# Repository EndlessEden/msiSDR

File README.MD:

# SDR RSP1: SIMPLIFIED 

## DESCRIPTION

(EXPECT THIS TO BE A MESS. It's direct from my research notes!)

"SDR RSP1 Simple" often referred to by "BG7YZF", is a SDRPlay RSP1/RSP1a clone with a simplified circuit. The SDR RSP1 is a redesign of the [MSI.SDR](https://github.com/11tools/msiSDR), a clone of the SDRplay RSP1A. All of these use the Msi001 and the Msi2500 (Sometimes called Msi3001 when used in this combo) chips which according to the vendor the SDR.RSP1 "Based on a simple small production made by Gao Wan"

----------------------

## HARDWARE

In a nutshell, it's a SDR receiver with 5 bandpass filtered antenna inputs and a USB Type-C interface. With no automatic antenna switching, and soldered in-line bandpass filters.

The [msi001](./Datasheets/msi001%20datasheet.pdf) microcircuit contains 5 antenna amplifiers (each for its own range), a synthesizer and quadrature mixers outputting I/Q signals, software-controlled bandpass filters and amplifiers. 

The [msi2500](./Datasheets/msi2500%20datasheet.pdf) is a variable bit (8 to 14 bit) ADC and DSP with USB interface. 

The result is:
- a range from 10 kHz to 1 GHz (with a hole at 250-400 MHz)
- a bandwidth of up to 10 MHz,
MSPS from 2 to 6 MHz (14-bit),
MSPS from 6 to 8 MHz (12-bit),
MSPS from 8 to 9 MHz (10 bits),
MSPS from 9 to 10 MHz (8 bits).
- With a SNR of 60 dB.

the "SDR RSP1" comes in two different models. ["Simple"](https://world.taobao.com/item/647736653771.htm?spm=a21wu.11804641.0.0.508e39d3yTvEJb) and ["Full"](https://www.taobao.com/list/item/645090109900.htm), their antenna circuitry, oscillators and filtering are different. The "Full" is notably better due to being simpler to operate, having a better oscillator and improved filtering. But all of these are design choices to cut costs. Outside the headaches with the Msi001's antenna switching, all other changes done to the "Full" version are entirely possible on the "Simple" version. Some of this can be done by the user if they are experienced in SMP soldering.

----------------------

## FROM THE VENDOR

[Vendor 2](https://world.taobao.com/item/647736653771.htm?spm=a21wu.11804641.0.0.508e39d3yTvEJb) "Question: What is the difference between this(SDR RSP1 Simple) and the full (SDR RSP1 full) version you sell?"
"Answer: The full version uses 0.5PPM TCXO (Oscillators), the frequency is accurate, the simple version only uses ordinary active crystal oscillators with a small offset (not affecting reception), the simple version does not have a casing, and the antenna needs to be switched manually. The simple version is only for usability. Pursue performance. The maximum frequency of the simple version can only reach 1G, you can change it to 2G by yourself(oscillator), because the simple version has a great simplification in the circuit, and it is not as good as the full version in terms of acceptance sensitivity and selectivity, but the two are the same in function Yes ..."

[Vendor 2](https://world.taobao.com/item/647736653771.htm?spm=a21wu.11804641.0.0.508e39d3yTvEJb) "Question: Did you design this yourself, or plagiarize someone else's circuit?"
"Answer: This SDR is an open source project of the foreign SDRPLAY company. The circuit has been simplified by the smith of the domestic science and technology forum. It is also open sourced. Here is the original post [www.kechuang.org/t/83757](www.kechuang.org/t/83757). Please refer to it. I just like radio. , Try to re-engrave it by yourself and add filters in the three bands of 60MHz to 1000Mhz, redesign the PCB layout, modify the interface to Type-C, no copper in the radio frequency area, and add jumper vias to facilitate later toss."

[Vendor 3](https://www.taobao.com/list/item/645090109900.htm) "This (SDR RSP1 Full) full version has the same software functions as the simple version ("SDR RSP1 Simple"), with higher sensitivity and more powerful performance."

----------------------

## ORIGIN

The "SDR RSP1 Simple" design originates from Huanghuai University(MAKER SPACE OF HUANGHUAI UNIVERSITY[香港 创 客 空 闪])(* See HHU), research done by a member known as "Smith" on their "Domestic science and technology forum" (See [Design](https://www.kechuang.org/t/83757)). The SDR RSP1's are improvements to these designs by "BG7YZF". A self-described as "a computer science and technology undergraduate student who is engaged in radio, model aircraft, drone, and photography." on their vendor page.

The "DE BG7YZF" silk screen refers to the designer, BG7YZF (a unregistered callsign from China [DXCC Entity #318]) is from QTH Xincai County, Henan Province. [VideoD1](https://www.bilibili.com/video/BV1Co4y1D7R2/) 

The Prefix 'DE' is a Morse code abbreviation amateur radio operators use meaning "from" (See [DE-W](https://en.wikipedia.org/wiki/Amateur_radio_call_signs)). 

The vendor "家晨科創" [Jiachen Technology](https://world.taobao.com/dianpu/573333074.htm?spm=a21wu.12321156.shop-area.1.4170796aFrsOco) seems to be BG7YZF as their callsign is their literal [logo](./Images/vendor/vendor.jpg). Supporting images in the product pages suggest they are the legitimate Vendors of the board(s).

All this information is further reinforced by other silk screens on the board (See images below):

"Maker Space of Huanghuai University" (Self Explanatory)

"Research, Science, Technology and prepare to serve the motherland" (HHU Quote)

and "家晨科创" [https://t.bilibili.com/550480890268977421?tab=2](https://t.bilibili.com/550480890268977421?tab=2) This last one is literally "BG7YZF".

----------------------

### KNOWN CAVEATS

 - Software: As the 'SDR RSP1 Simple' is a modified MSI.SDR RSP1 design (Itself Based on the SDRplay RSP1A), the msi001 and msi2500 chips can natively use SDRplay's proprietary api. However, other projects based on libusb(see mirisdr4) have come along to attempt to interface with the device's raw I/Q stream Using similar methods to the now famous rtlsdr project. However, since the 'RSP1 Simple' is based on the 'RSP1A', i am unaware of how well supported it would be at this moment in time. (See: https://github.com/f4exb/libmirisdr-4/issues/2) 
 
 - Tuning: the SDR RSP1 Simple requires "manual antenna switching"(This is poorly documented!), unlike its "Full" version. As expected from its poorly documented nature, Users report "RSP1 Simple"/"BG7YZF" cannot tune out of FM broadcast frequency range (See: [Ref 1](https://forums.radioreference.com/threads/12-bit-4-antenna-ports-35-delivered.430252/page-2)/[Ref 3](https://www.reddit.com/r/RTLSDR/comments/onftps/any_feedback_on_the_bg7yzf_version_of_the_msi_001/)). Although reports show otherwise (See: [Ref 4](https://www.reddit.com/r/RTLSDR/comments/qnlfwq/rsp1_chinese_clone_reviewissues/)) | As mentioned, the antennas have to be manually "Switched", The Msi001 is entirely capable of tuning frequency separated antennas, thus its design. However, switching antenna sources seems to be something that has to be done at the msi001(Tuner)'s initialisation. This is all very poorly documented and even the vendor does not  document this properly. Only vaguely mentioning it in an additional "Faq" area at the bottom of their product advert... | I will review and document what i learn when i have more time to understand the issue. I have yet to test the device at all, so i have no idea of its functionality as of yet.
 
 - USB 2.0 Type-C: USB-C interface seems to have several datalines not connected, suggesting it can only achieve USB 2.0 "High-Speed" speeds. While this should be fine (in theory), it may limit bandwidth in some circumstances. The Msi2500's USB Interface is unknown to me at the time of writing, so its suggested it follows USB 1.1/2.0 specifications. limiting many factors including the length of the cable significantly. This is due to power limitations that USB2.0 specification lays out not allowing more than 5v/0.5A(500mA), or 2.5w power draw. This limitation prevents long cable lengths due to the loss experienced at 3M, limiting it to a theoretical maximum of 5m. | Something Usb3.0+ partially overcame with power specification changes. Most importantly this allows for in-line Active USB cables instead of passive, extending length to up to 50M with limited loss. All of this is mute if in fact Msi001 is usb 2.0 only, but if it is capable of 3.0, then the wiring is a design fault for certain.
 
 - Undocumented Variants: Design has Undocumented variants (See: [R4-E](https://www.ebay.com/itm/255106602228)) as seen in The Ebay listing shared in [Reference 4](https://www.reddit.com/r/RTLSDR/comments/qnlfwq/rsp1_chinese_clone_reviewissues/). It shows a model that has different silkscreening and what appears to be slightly different design choices. None of this is documented and the seller shows the device as "New". This may be a clone/counterfeit, But i can't confirm or deny any of this. - No user images have surfaced of this device in use and very little information of SDR RSP1 Simple in use exists in general. While some testing exists of the SDR RSP1 Full, the simplified is overlooked due to its undocumented caveats surround the antenna inputs.
 
 - Case: The SDR RSP1 Simple doesn't have or come with a vendor supplied case. This is a design choice as the "Simple" version is supposed to be an educational kit clearly. 
 However, a case DOES exist on thingiverse. 

----------------------

## FURTHER IMAGES:

--------------------------------------------------------------------------------------

# GLOSSARY

Ref 1: https://forums.radioreference.com/threads/12-bit-4-antenna-ports-35-delivered.430252/page-2 (archived: https://web.archive.org/web/20211124164150/https://forums.radioreference.com/threads/12-bit-4-antenna-ports-35-delivered.430252/page-2)

Ref 2: http://hamforum.ru/viewtopic.php?t=725 (archived: https://web.archive.org/web/20211124164546/http://hamforum.ru/viewtopic.php?t=725)

Ref 3: https://www.reddit.com/r/RTLSDR/comments/onftps/any_feedback_on_the_bg7yzf_version_of_the_msi_001/ (archived: https://web.archive.org/web/20211124182343/https://www.reddit.com/r/RTLSDR/comments/onftps/any_feedback_on_the_bg7yzf_version_of_the_msi_001/)

Ref 4: https://www.reddit.com/r/RTLSDR/comments/qnlfwq/rsp1_chinese_clone_reviewissues/ (archived: https://web.archive.org/web/20211105214824/https://www.reddit.com/r/RTLSDR/comments/qnlfwq/rsp1_chinese_clone_reviewissues/) | the ebay listing and album are archived as well

R4-E: https://www.ebay.com/itm/255106602228 (archived: https://www.ebay.com/itm/255106602228) [Taken from Ref 4's post]

R4-A: https://imgur.com/a/kOgz7DM (archived: https://web.archive.org/web/20211118155743/https://imgur.com/a/kOgz7DM) [Taken from Ref 4's post]

Mirisdr4: https://github.com/f4exb/libmirisdr-4 (archived: https://web.archive.org/web/20211124170317/https://github.com/f4exb/libmirisdr-4)

Case: https://www.thingiverse.com/thing:4988416 (archived: https://web.archive.org/web/20211124205033/https://www.thingiverse.com/thing:4988416)

DE-W: https://en.wikipedia.org/wiki/Amateur_radio_call_signs

HHU: http://cms2.huanghuai.edu.cn/s.php/english/item-view-id-21110.html

HHU-2: http://cms2.huanghuai.edu.cn/s.php/english/item-view-id-39020.html

Design: https://www.kechuang.org/t/83757 (archived: https://web.archive.org/web/20211124211743/https://www.kechuang.org/t/83757) *(Translated: https://world.taobao.com/item/647736653771.htm?spm=a21wu.11804641.0.0.508e39d3WbK6VD)

Vendor 1: https://world.taobao.com/dianpu/573333074.htm?spm=a21wu.12321156.shop-area.1.4170796aFrsOco (archived: https://world.taobao.com/dianpu/573333074.htm?spm=a21wu.12321156.shop-area.1.4170796aFrsOco)

Vendor 2: https://world.taobao.com/item/647736653771.htm?spm=a21wu.11804641.0.0.508e39d3yTvEJb (archived: https://web.archive.org/web/20211124164116/https://world.taobao.com/item/647736653771.htm?spm=a21wu.11804641.0.0.508e39d3yTvEJb)

Vendor 3: https://www.taobao.com/list/item/645090109900.htm (archived: https://web.archive.org/web/20211124164116/https://www.taobao.com/list/item/645090109900.htm)

VideoD1: https://www.bilibili.com/video/BV1Co4y1D7R2/ (archived: https://web.archive.org/web/20211124164152/https://www.bilibili.com/video/BV1Co4y1D7R2/)

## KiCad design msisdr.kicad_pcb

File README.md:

this is an Software Define Radio receiver PCB project base on msi2500 and msi001. use kicad to view it

这是一个基于msi2500 和 msi001的软件无线电PCB工程项目， 使用kiCAD浏览此工程

如果需要PCB打样，把gerber目录下的文件发给PCB加工厂即可

Send gerbar files to PCB factory . you'd better to use SMT

建议叫工厂SMT贴片，手动焊接容易太多bug

软件使用SDRuno（选SDRPlay）

software compatible with SDRplay

## Updates from NaiveTomcat
在原版的基础上增加了一个U.FL接口用于L波段天线的连接（才不会说是懒得重新
布线才用U.FL接口的呢）Gerber文件在Gerberv3目录

Added a U.FL Male socket onto the PCB for aerials for L-Band.
(Used U.FL for its size can fit inside the board with no need
to redo the route) Gerber files are in the Gerberv3 directory.

使用效果

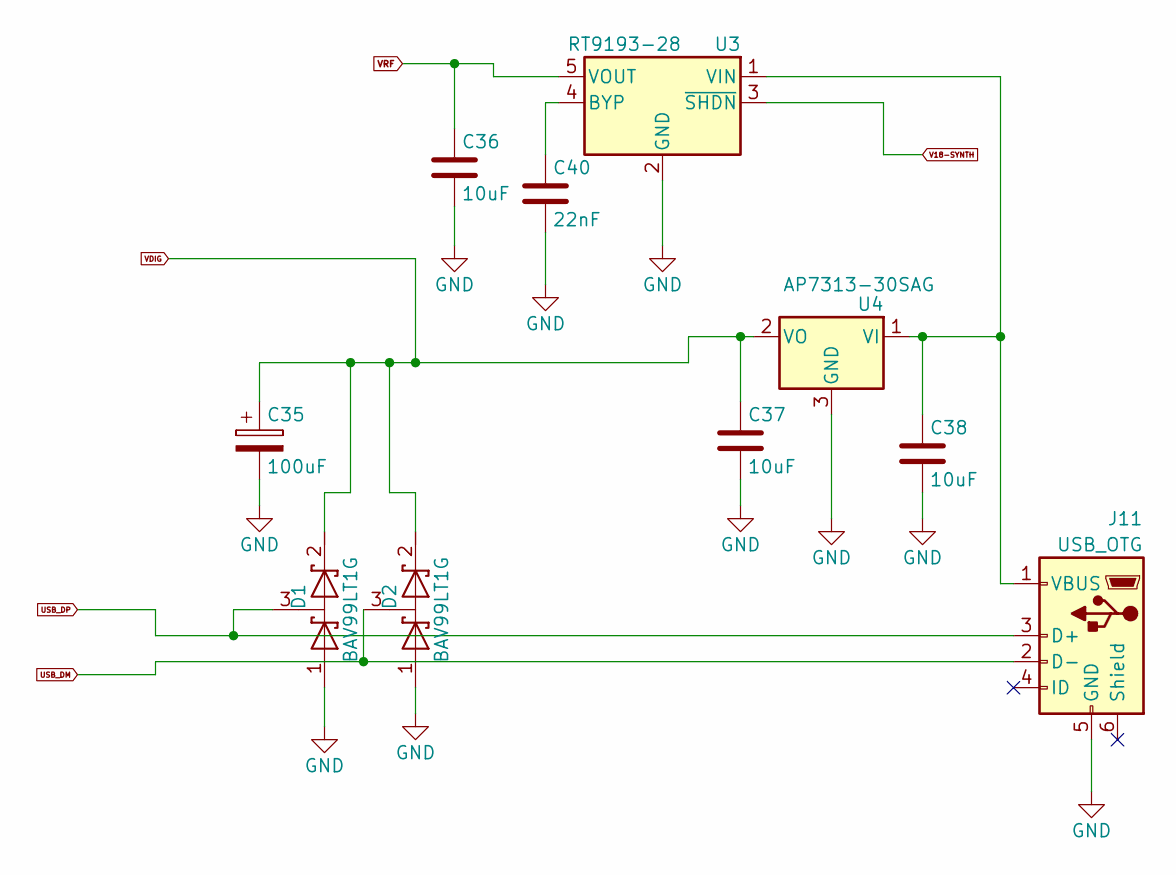
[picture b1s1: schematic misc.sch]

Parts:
C35: 100uF; CP_Radial_D5.0mm_P2.50mm
C36, C37, C38: 10uF; C_1206_3216Metric_Pad1.33x1.80mm_HandSolder
C40: 22nF; C_1206_3216Metric_Pad1.33x1.80mm_HandSolder
D1, D2: BAV99LT1G; SOT-23
J11: USB_OTG; USB_Micro-B_Wuerth_629105150521
U3: RT9193-28; SOT-23-5
U4: AP7313-30SAG; SOT-23

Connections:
GND: C35.2, C36.2, C37.2, C38.2, C40.2, D1.1 (A), D2.1 (A), J11.5 (GND), U3.2 (GND), U4.3 (GND); also elsewhere on the board
unnamed: C38.1, J11.1 (VBUS), U3.1 (VIN), U4.1 (VI)
unnamed: C40.1, U3.4 (BYP)
USB_DM: D2.3 (common), J11.2 (D-); also elsewhere on the board
USB_DP: D1.3 (common), J11.3 (D+); also elsewhere on the board
V18-SYNTH: U3.3 (~SHDN~); also elsewhere on the board
VDIG: C35.1, C37.1, D1.2 (K), D2.2 (K), U4.2 (VO); also elsewhere on the board
VRF: C36.1, U3.5 (VOUT); also elsewhere on the board

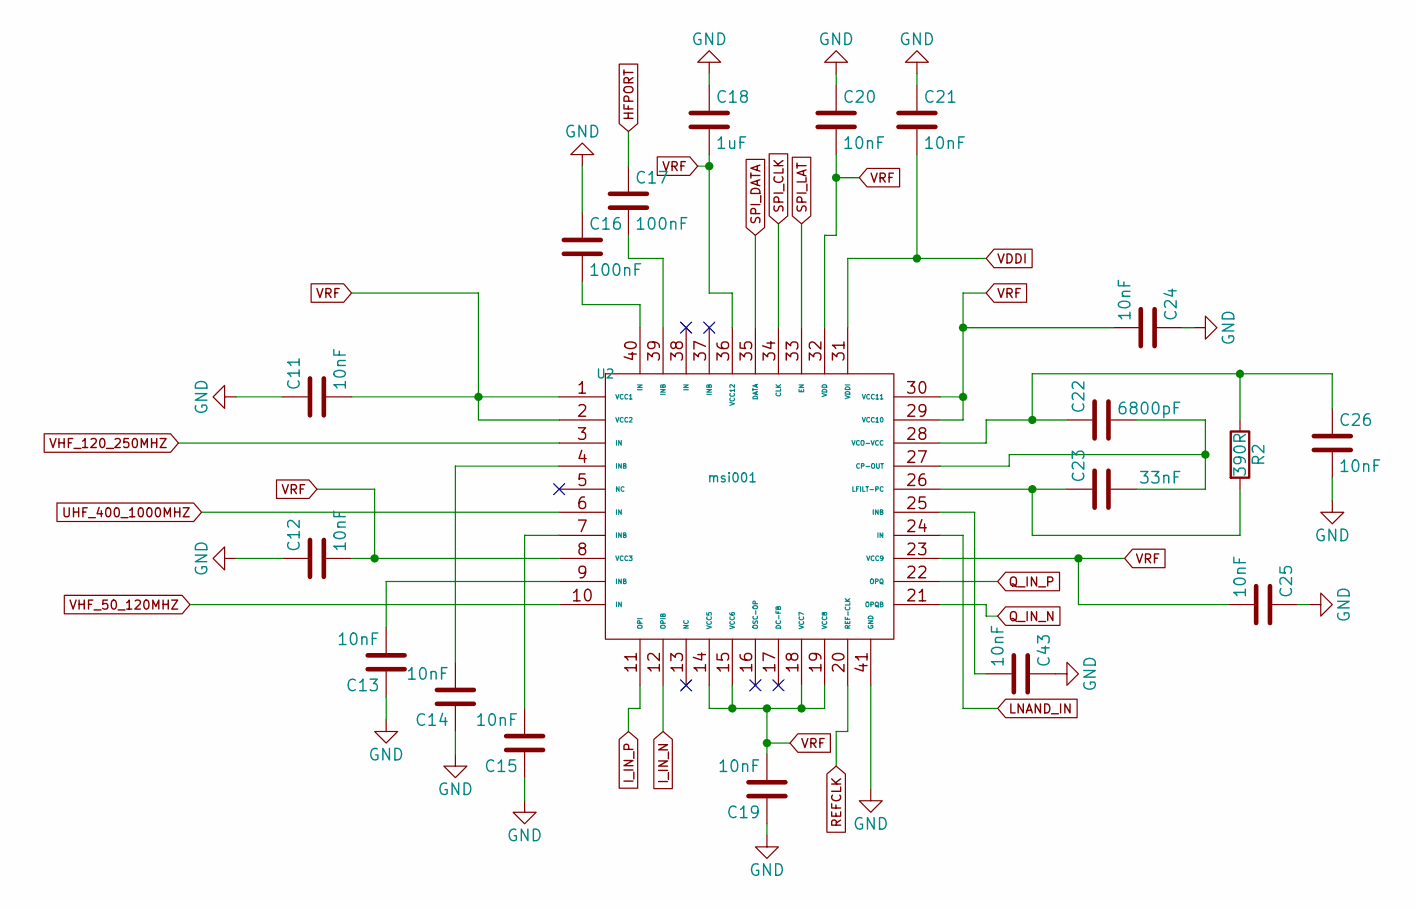
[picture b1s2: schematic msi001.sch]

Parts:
C11, C12, C13, C14, C15, C19, C20, C21, C24, C25, C26, C43: 10nF; C_1206_3216Metric_Pad1.33x1.80mm_HandSolder
C16, C17: 100nF; C_1206_3216Metric_Pad1.33x1.80mm_HandSolder
C18: 1uF; C_1206_3216Metric_Pad1.33x1.80mm_HandSolder
C22: 6800pF; C_1206_3216Metric_Pad1.33x1.80mm_HandSolder
C23: 33nF; C_1206_3216Metric_Pad1.33x1.80mm_HandSolder
R2: 390R; R_1206_3216Metric_Pad1.30x1.75mm_HandSolder
U2: msi001; QFN-40-1EP_6x6mm_P0.5mm_EP4.6x4.6mm_ThermalVias

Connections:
GND: C11.1, C12.1, C13.1, C14.1, C15.1, C16.1, C18.1, C19.1, C20.1, C21.1, C24.1, C25.1, C26.2, C43.1, U2.41 (GND); also elsewhere on the board
HFPORT: C17.1; also elsewhere on the board
I_IN_N: U2.12 (OPIB); also elsewhere on the board
I_IN_P: U2.11 (OPI); also elsewhere on the board
LNAND_IN: U2.24 (IN); also elsewhere on the board
unnamed: C13.2, U2.9 (INB)
unnamed: C14.2, U2.4 (INB)
unnamed: C15.2, U2.7 (INB)
unnamed: C16.2, U2.40 (IN)
unnamed: C17.2, U2.39 (INB)
unnamed: C22.1, C26.1, R2.1, U2.28 (VCO-VCC)
unnamed: C22.2, C23.2, U2.27 (CP-OUT)
unnamed: C23.1, R2.2, U2.26 (LFILT-PC)
unnamed: C43.2, U2.25 (INB)
Q_IN_N: U2.21 (OPQB); also elsewhere on the board
Q_IN_P: U2.22 (OPQ); also elsewhere on the board
REFCLK: U2.20 (REF-CLK); also elsewhere on the board
SPI_CLK: U2.34 (CLK); also elsewhere on the board
SPI_DATA: U2.35 (DATA); also elsewhere on the board
SPI_LAT: U2.33 (EN); also elsewhere on the board
UHF_400_1000MHZ: U2.6 (IN); also elsewhere on the board
VDDI: C21.2, U2.31 (VDDI); also elsewhere on the board
VHF_50_120MHZ: U2.10 (IN); also elsewhere on the board
VHF_120_250MHZ: U2.3 (IN); also elsewhere on the board
VRF: C11.2, C12.2, C18.2, C19.2, C20.2, C24.2, C25.2, U2.1 (VCC1), U2.2 (VCC2), U2.8 (VCC3), U2.14 (VCC5), U2.15 (VCC6), U2.18 (VCC7), U2.19 (VCC8), U2.23 (VCC9), U2.29 (VCC10), U2.30 (VCC11), U2.32 (VDD), U2.36 (VCC12); also elsewhere on the board

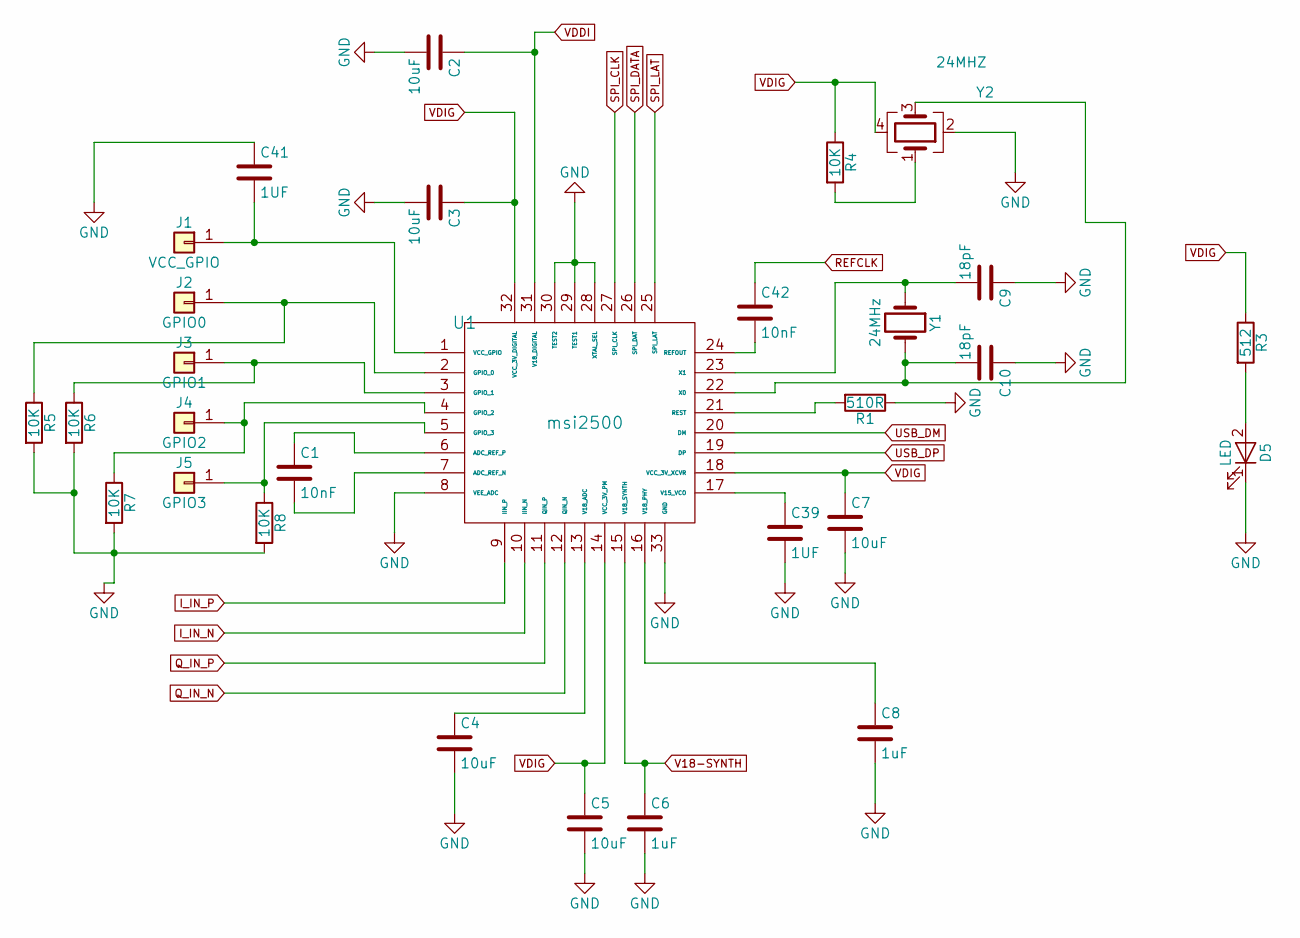
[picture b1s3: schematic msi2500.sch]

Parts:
C1, C42: 10nF; C_1206_3216Metric_Pad1.33x1.80mm_HandSolder
C2, C3, C4, C5, C7: 10uF; C_1206_3216Metric_Pad1.33x1.80mm_HandSolder
C6, C8: 1uF; C_1206_3216Metric_Pad1.33x1.80mm_HandSolder
C9, C10: 18pF; C_1206_3216Metric_Pad1.33x1.80mm_HandSolder
C39, C41: 1UF; C_1206_3216Metric_Pad1.33x1.80mm_HandSolder
D5: LED; D_DO-35_SOD27_P2.54mm_Vertical_AnodeUp
J1: VCC_GPIO; Pin_D0.7mm_L6.5mm_W1.8mm_FlatFork
J2: GPIO0; Pin_D0.7mm_L6.5mm_W1.8mm_FlatFork
J3: GPIO1; Pin_D0.7mm_L6.5mm_W1.8mm_FlatFork
J4: GPIO2; Pin_D0.7mm_L6.5mm_W1.8mm_FlatFork
J5: GPIO3; Pin_D0.7mm_L6.5mm_W1.8mm_FlatFork
R1: 510R; R_1206_3216Metric_Pad1.30x1.75mm_HandSolder
R3: 512; R_1206_3216Metric_Pad1.30x1.75mm_HandSolder
R4, R5, R6, R7, R8: 10K; R_1206_3216Metric_Pad1.30x1.75mm_HandSolder
U1: msi2500; QFN-32-1EP_5x5mm_P0.5mm_EP3.7x3.7mm_ThermalVias
Y1: 24MHz; Crystal_HC50_Vertical
Y2: 24MHZ; Crystal_SMD_7050-4Pin_7.0x5.0mm

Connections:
GND: C2.2, C3.2, C4.2, C5.2, C6.2, C7.2, C8.2, C9.1, C10.1, C39.2, C41.1, D5.1 (K), R1.1, R5.2, R6.2, R7.2, R8.2, U1.8 (VEE_ADC), U1.28 (XTAL_SEL), U1.29 (TEST1), U1.30 (TEST2), U1.33 (GND), Y2.2; also elsewhere on the board
I_IN_N: U1.10 (IIN_N); also elsewhere on the board
I_IN_P: U1.9 (IIN_P); also elsewhere on the board
unnamed: C1.1, U1.6 (ADC_REF_P)
unnamed: C1.2, U1.7 (ADC_REF_N)
unnamed: C4.1, U1.13 (V18_ADC)
unnamed: C8.1, U1.16 (V18_PHY)
unnamed: C9.2, U1.23 (X1), Y1.1
unnamed: C10.2, U1.22 (X0), Y1.2, Y2.3
unnamed: C39.1, U1.17 (V15_VCO)
unnamed: C41.2, J1.1, U1.1 (VCC_GPIO)
unnamed: C42.2, U1.24 (REFOUT)
unnamed: D5.2 (A), R3.2
unnamed: J2.1, R5.1, U1.2 (GPIO_0)
unnamed: J3.1, R6.1, U1.3 (GPIO_1)
unnamed: J4.1, R7.1, U1.4 (GPIO_2)
unnamed: J5.1, R8.1, U1.5 (GPIO_3)
unnamed: R1.2, U1.21 (REST)
unnamed: R4.2, Y2.1
Q_IN_N: U1.12 (QIN_N); also elsewhere on the board
Q_IN_P: U1.11 (QIN_P); also elsewhere on the board
REFCLK: C42.1; also elsewhere on the board
SPI_CLK: U1.27 (SPI_CLK); also elsewhere on the board
SPI_DATA: U1.26 (SPI_DAT); also elsewhere on the board
SPI_LAT: U1.25 (SPI_LAT); also elsewhere on the board
USB_DM: U1.20 (DM); also elsewhere on the board
USB_DP: U1.19 (DP); also elsewhere on the board
V18-SYNTH: C6.1, U1.15 (V18_SYNTH); also elsewhere on the board
VDDI: C2.1, U1.31 (V18_DIGITAL); also elsewhere on the board
VDIG: C3.1, C5.1, C7.1, R3.1, R4.1, U1.14 (VCC_3V_PM), U1.18 (VCC_3V_XCVR), U1.32 (VCC_3V_DIGITAL), Y2.4; also elsewhere on the board

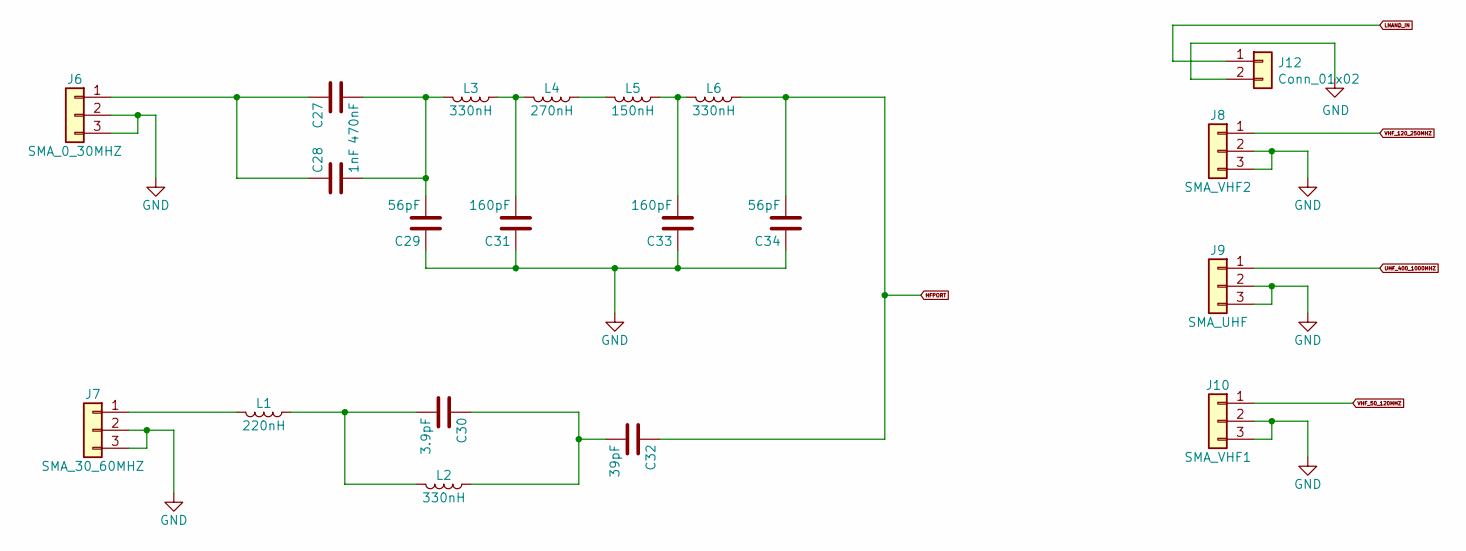
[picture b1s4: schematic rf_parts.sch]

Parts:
C27: 470nF; C_1206_3216Metric_Pad1.33x1.80mm_HandSolder
C28: 1nF; C_1206_3216Metric_Pad1.33x1.80mm_HandSolder
C29, C34: 56pF; C_1206_3216Metric_Pad1.33x1.80mm_HandSolder
C30: 3.9pF; C_1206_3216Metric_Pad1.33x1.80mm_HandSolder
C31, C33: 160pF; C_1206_3216Metric_Pad1.33x1.80mm_HandSolder
C32: 39pF; C_1206_3216Metric_Pad1.33x1.80mm_HandSolder
J6: SMA_0_30MHZ; SMA_Samtec_SMA-J-P-X-ST-EM1_EdgeMount
J7: SMA_30_60MHZ; SMA_Samtec_SMA-J-P-X-ST-EM1_EdgeMount
J8: SMA_VHF2; SMA_Samtec_SMA-J-P-X-ST-EM1_EdgeMount
J9: SMA_UHF; SMA_Samtec_SMA-J-P-X-ST-EM1_EdgeMount
J10: SMA_VHF1; SMA_Samtec_SMA-J-P-X-ST-EM1_EdgeMount
J12: Conn_01x02; U.FL_Molex_MCRF_73412-0110_Vertical
L1: 220nH; L_1206_3216Metric_Pad1.42x1.75mm_HandSolder
L2, L3, L6: 330nH; L_1206_3216Metric_Pad1.42x1.75mm_HandSolder
L4: 270nH; L_1206_3216Metric_Pad1.42x1.75mm_HandSolder
L5: 150nH; L_1206_3216Metric_Pad1.42x1.75mm_HandSolder

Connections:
GND: C29.1, C31.1, C33.1, C34.1, J6.2, J6.3, J7.2, J7.3, J8.2, J8.3, J9.2, J9.3, J10.2, J10.3, J12.2; also elsewhere on the board
HFPORT: C32.1, C34.2, L6.1; also elsewhere on the board
LNAND_IN: J12.1; also elsewhere on the board
unnamed: C27.1, C28.1, J6.1
unnamed: C27.2, C28.2, C29.2, L3.2
unnamed: C30.1, C32.2, L2.1
unnamed: C30.2, L1.1, L2.2
unnamed: C31.2, L3.1, L4.2
unnamed: C33.2, L5.1, L6.2
unnamed: J7.1, L1.2
unnamed: L4.1, L5.2
UHF_400_1000MHZ: J9.1; also elsewhere on the board
VHF_50_120MHZ: J10.1; also elsewhere on the board
VHF_120_250MHZ: J8.1; also elsewhere on the board

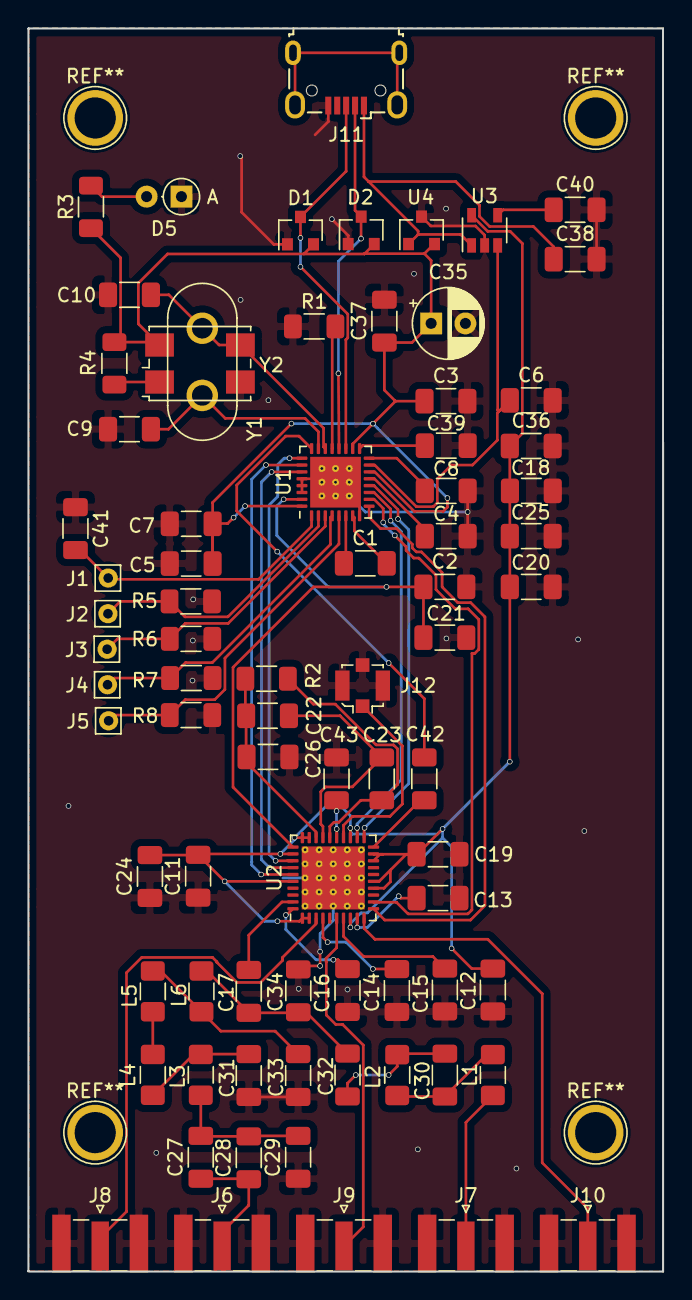
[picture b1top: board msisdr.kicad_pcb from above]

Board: 2 copper layers, 46.3 x 90.7 mm, 78 parts (0 on the bottom side), 55 nets.

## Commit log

2020-12-01 Added an U.FL male socket for L Band antanae
2020-12-02 Fixed clearance issue
2020-12-04 Changed the package of R, C and L to 1206 for hand soldering.
2020-12-04 Added gerber files
2020-12-04 added bom
2021-11-24 Initial commit on orphan branch
2021-11-24 Initial work to convert research notes into README.md. Added all gathered and taken Images.
2021-11-24 Immediate spacing correction
2021-11-24 Will the Real README.MD, please stand up...
2021-11-24 Cleanup and formatting
2021-11-24 Typo (Small)
2021-11-24 Text editors and space bars...
2021-11-24 Added: media, Fixed: Markdown in README
2021-11-24 Fixed: Markdown in README
2021-11-24 Fixed: Markdown in README...again?
2021-11-24 Fixed: Markdown in README...%20?
2021-11-24 More Markdown, added resources.
2021-11-24 Removed: Uneccessary break Line
2021-11-24 Cleaned: markup more.
2021-11-24 Cleaned: bad link.
2021-11-24 Litteracy: Who needs Litteracy when you have...
2021-11-24 Litteracy: More Cleaning and markup
2021-11-24 Litteracy: More Cleaning and markup,2.
2021-11-24 Markup: Doin' it live and in Githubs
2021-11-24 Markup: Fixing Referrals
2021-11-24 Markup: Fixing Referrals,2
2021-11-24 Typo: 'a' on line 85, and image?
2021-11-24 85: image hyper link
2021-11-24 85: Mistakes were made... correction be had.
2021-11-24 85: Size, Matters..
2021-11-24 85: Size, Matters?..
2021-11-24 85: html size, Matters?
2021-11-24 85: html vs markup, size Matters...
2021-11-24 85: Enlightenment.
2021-11-24 85: Cleanup.
2021-11-24 107: missing bracket
2021-11-24 83: Where do i find a 'intenna'
2021-11-24 1: adding image
2021-11-24 1: fixing image
2021-11-24 1: fixing image width
2021-11-24 filechanges
2021-11-25 Fixed sentence doubling
